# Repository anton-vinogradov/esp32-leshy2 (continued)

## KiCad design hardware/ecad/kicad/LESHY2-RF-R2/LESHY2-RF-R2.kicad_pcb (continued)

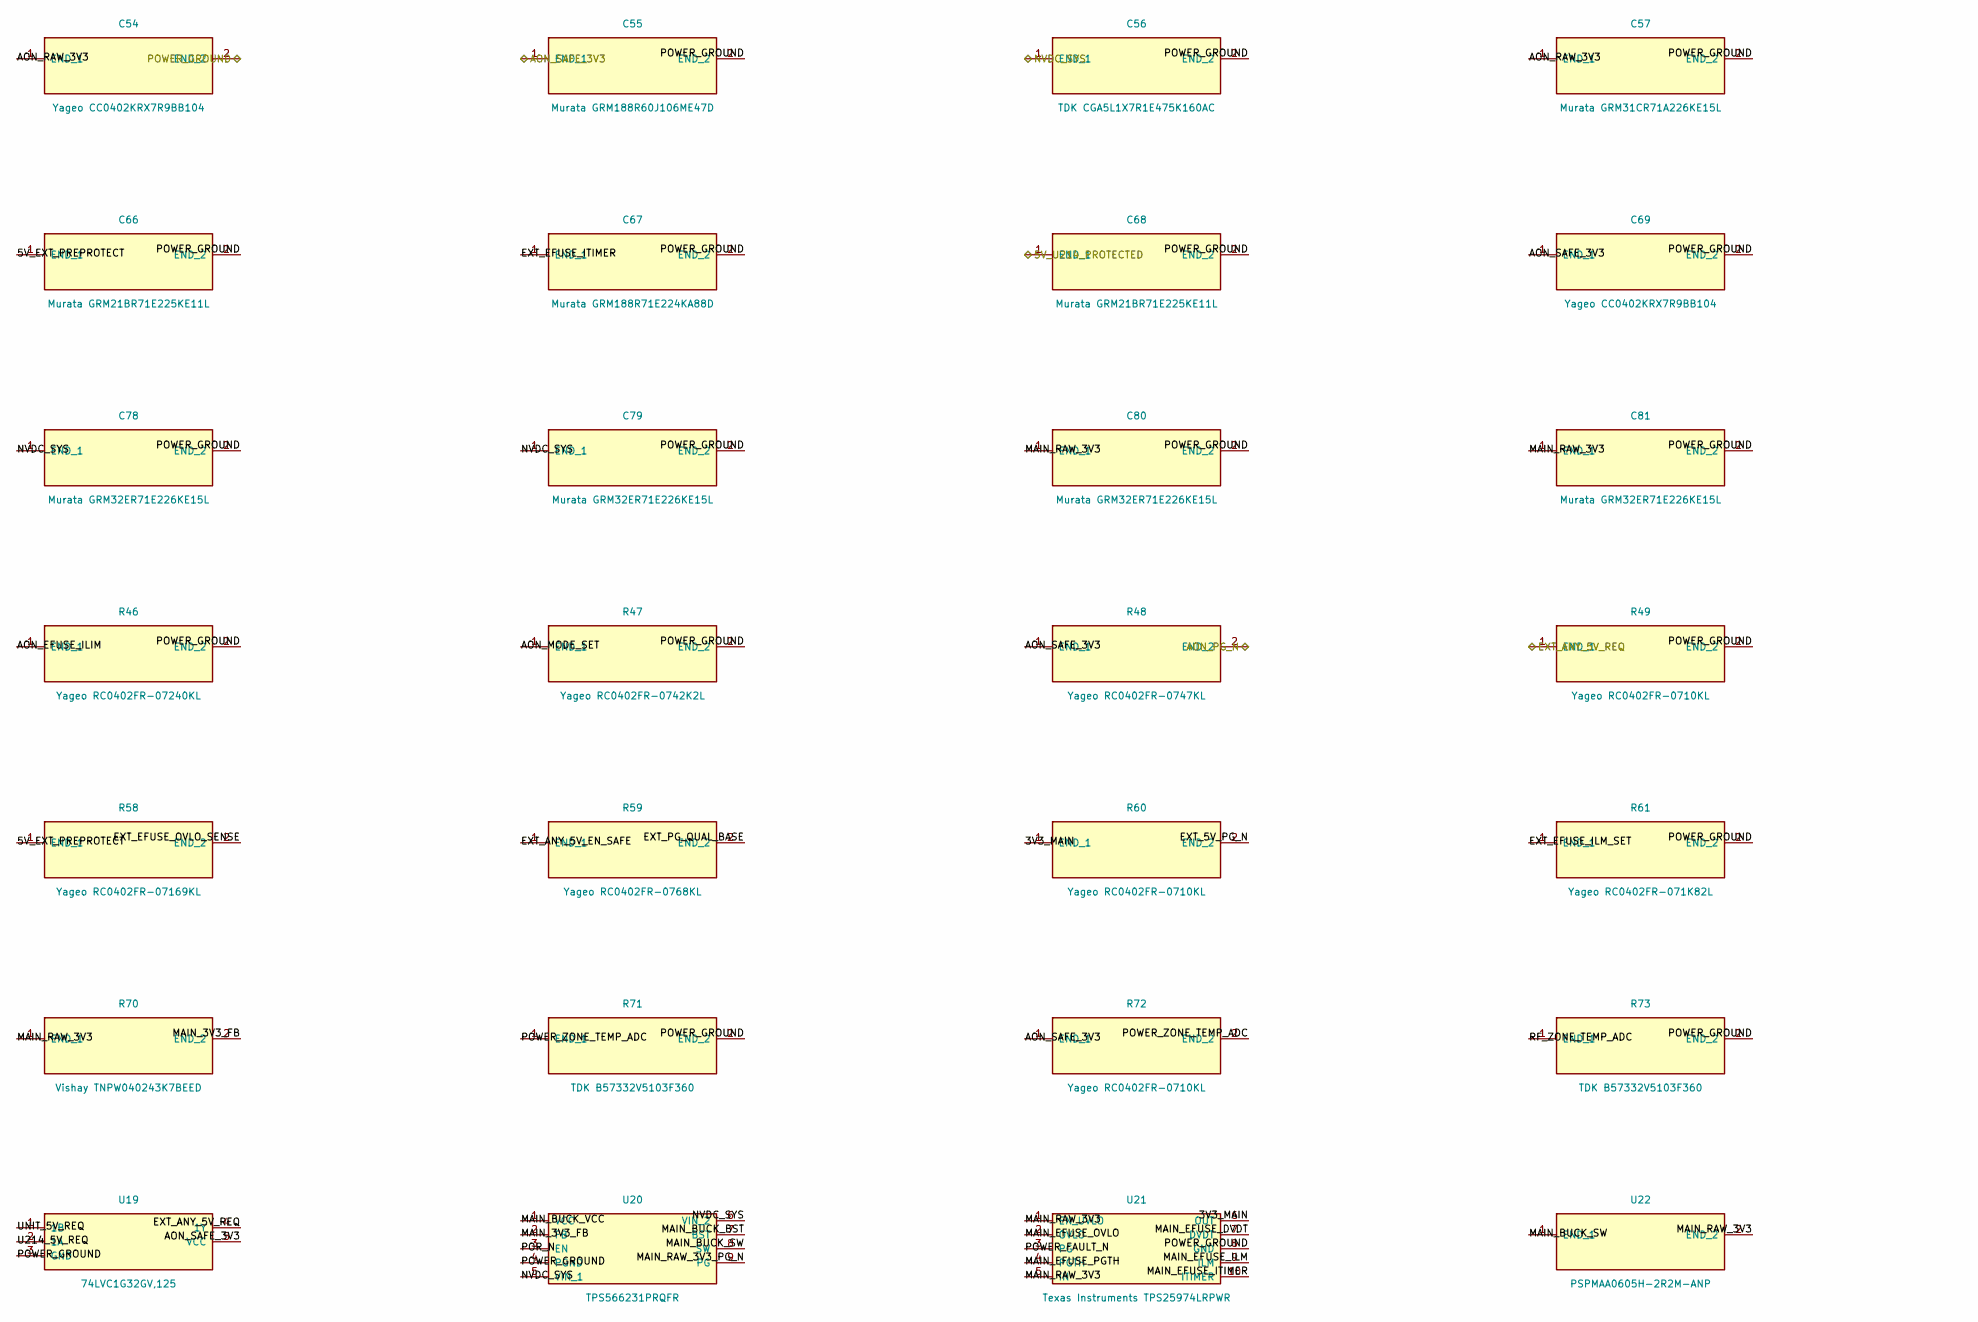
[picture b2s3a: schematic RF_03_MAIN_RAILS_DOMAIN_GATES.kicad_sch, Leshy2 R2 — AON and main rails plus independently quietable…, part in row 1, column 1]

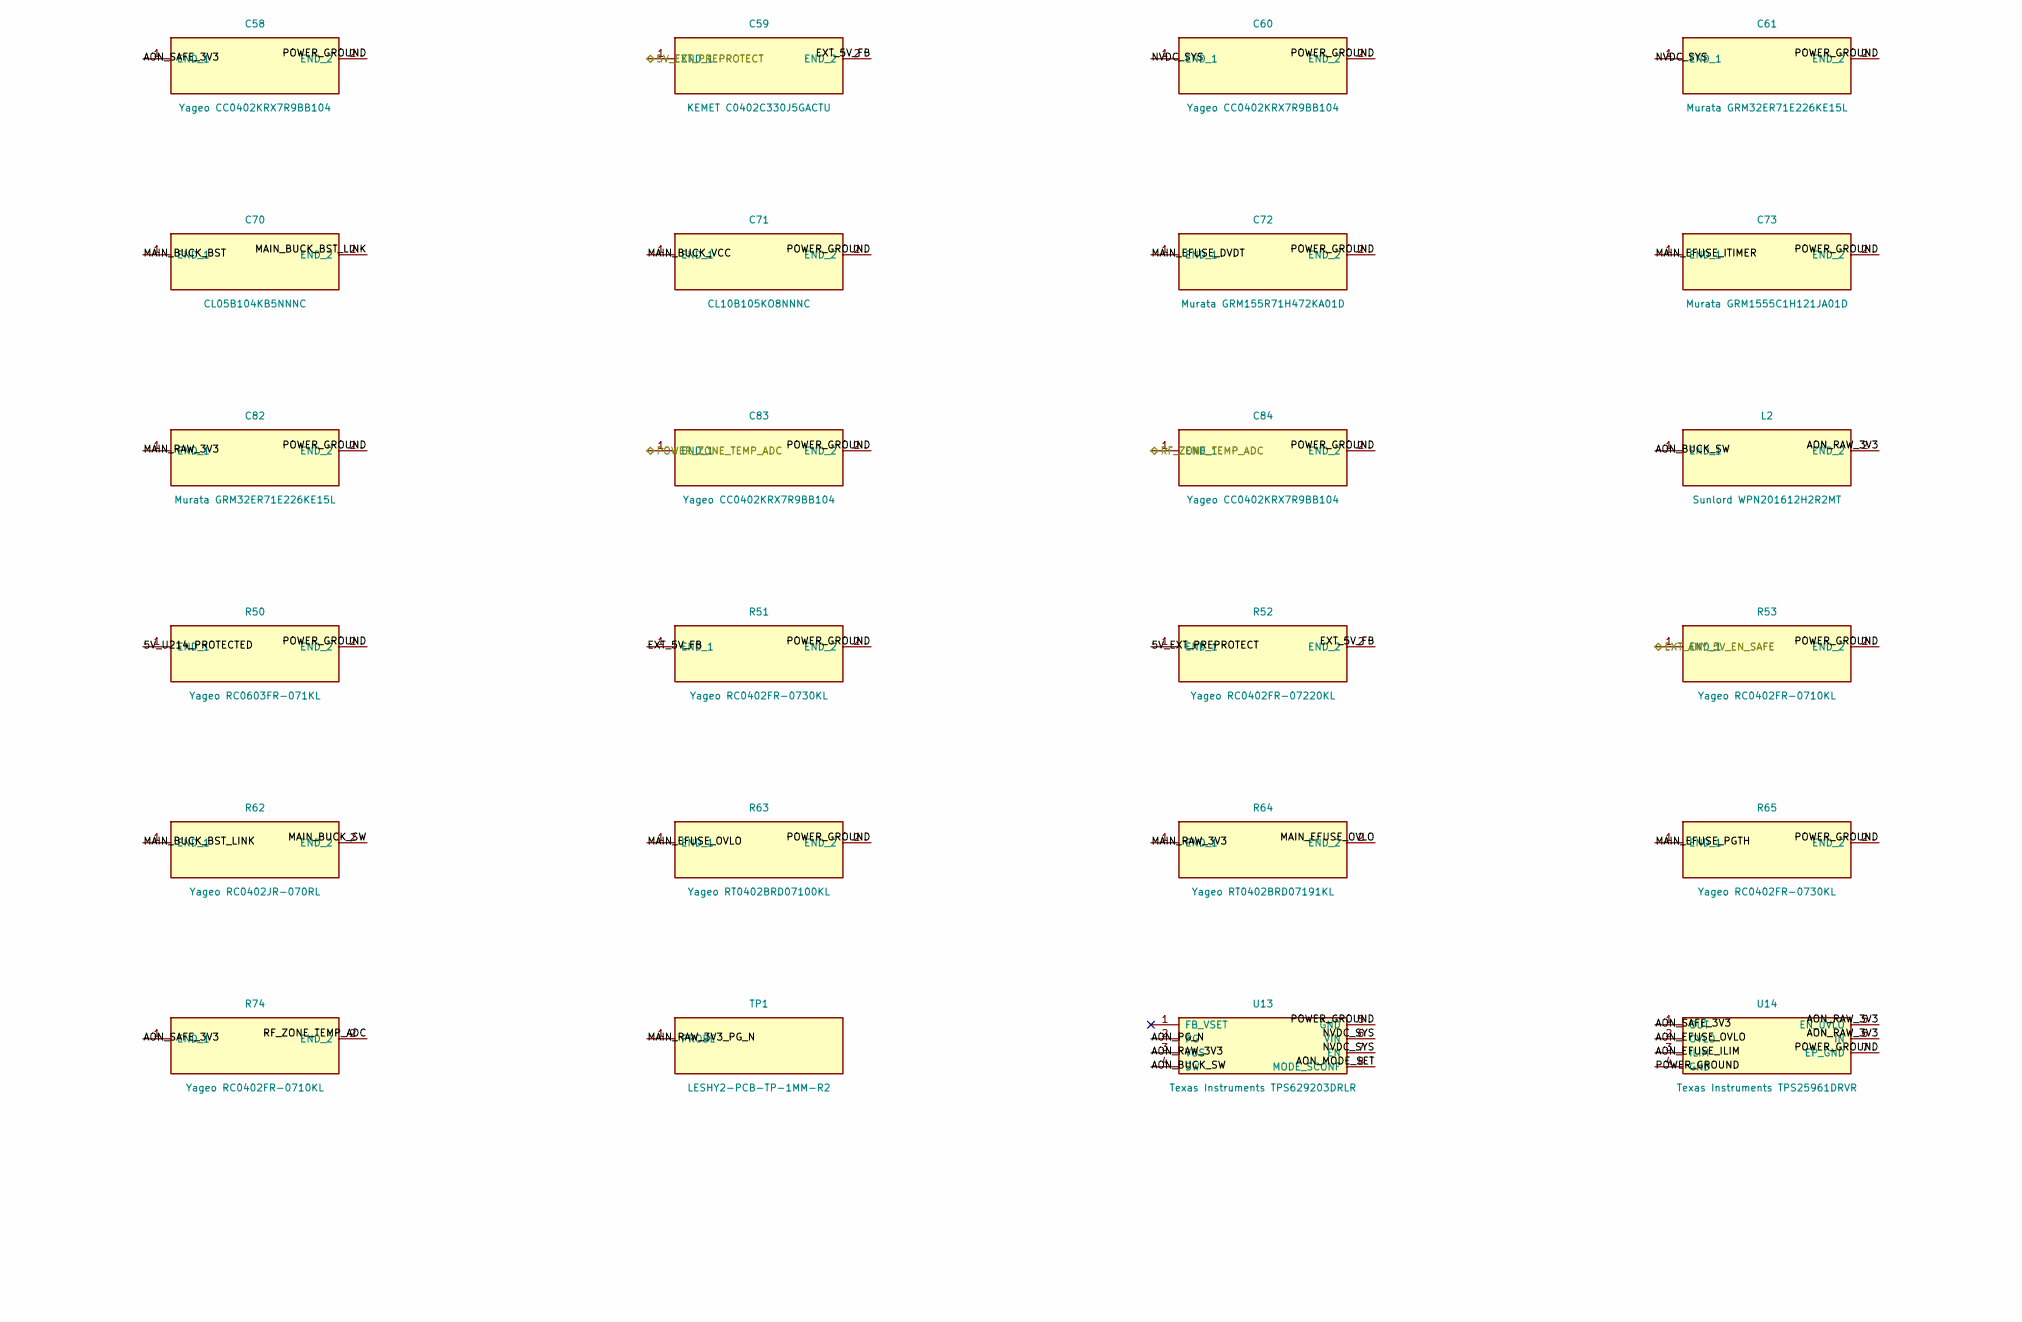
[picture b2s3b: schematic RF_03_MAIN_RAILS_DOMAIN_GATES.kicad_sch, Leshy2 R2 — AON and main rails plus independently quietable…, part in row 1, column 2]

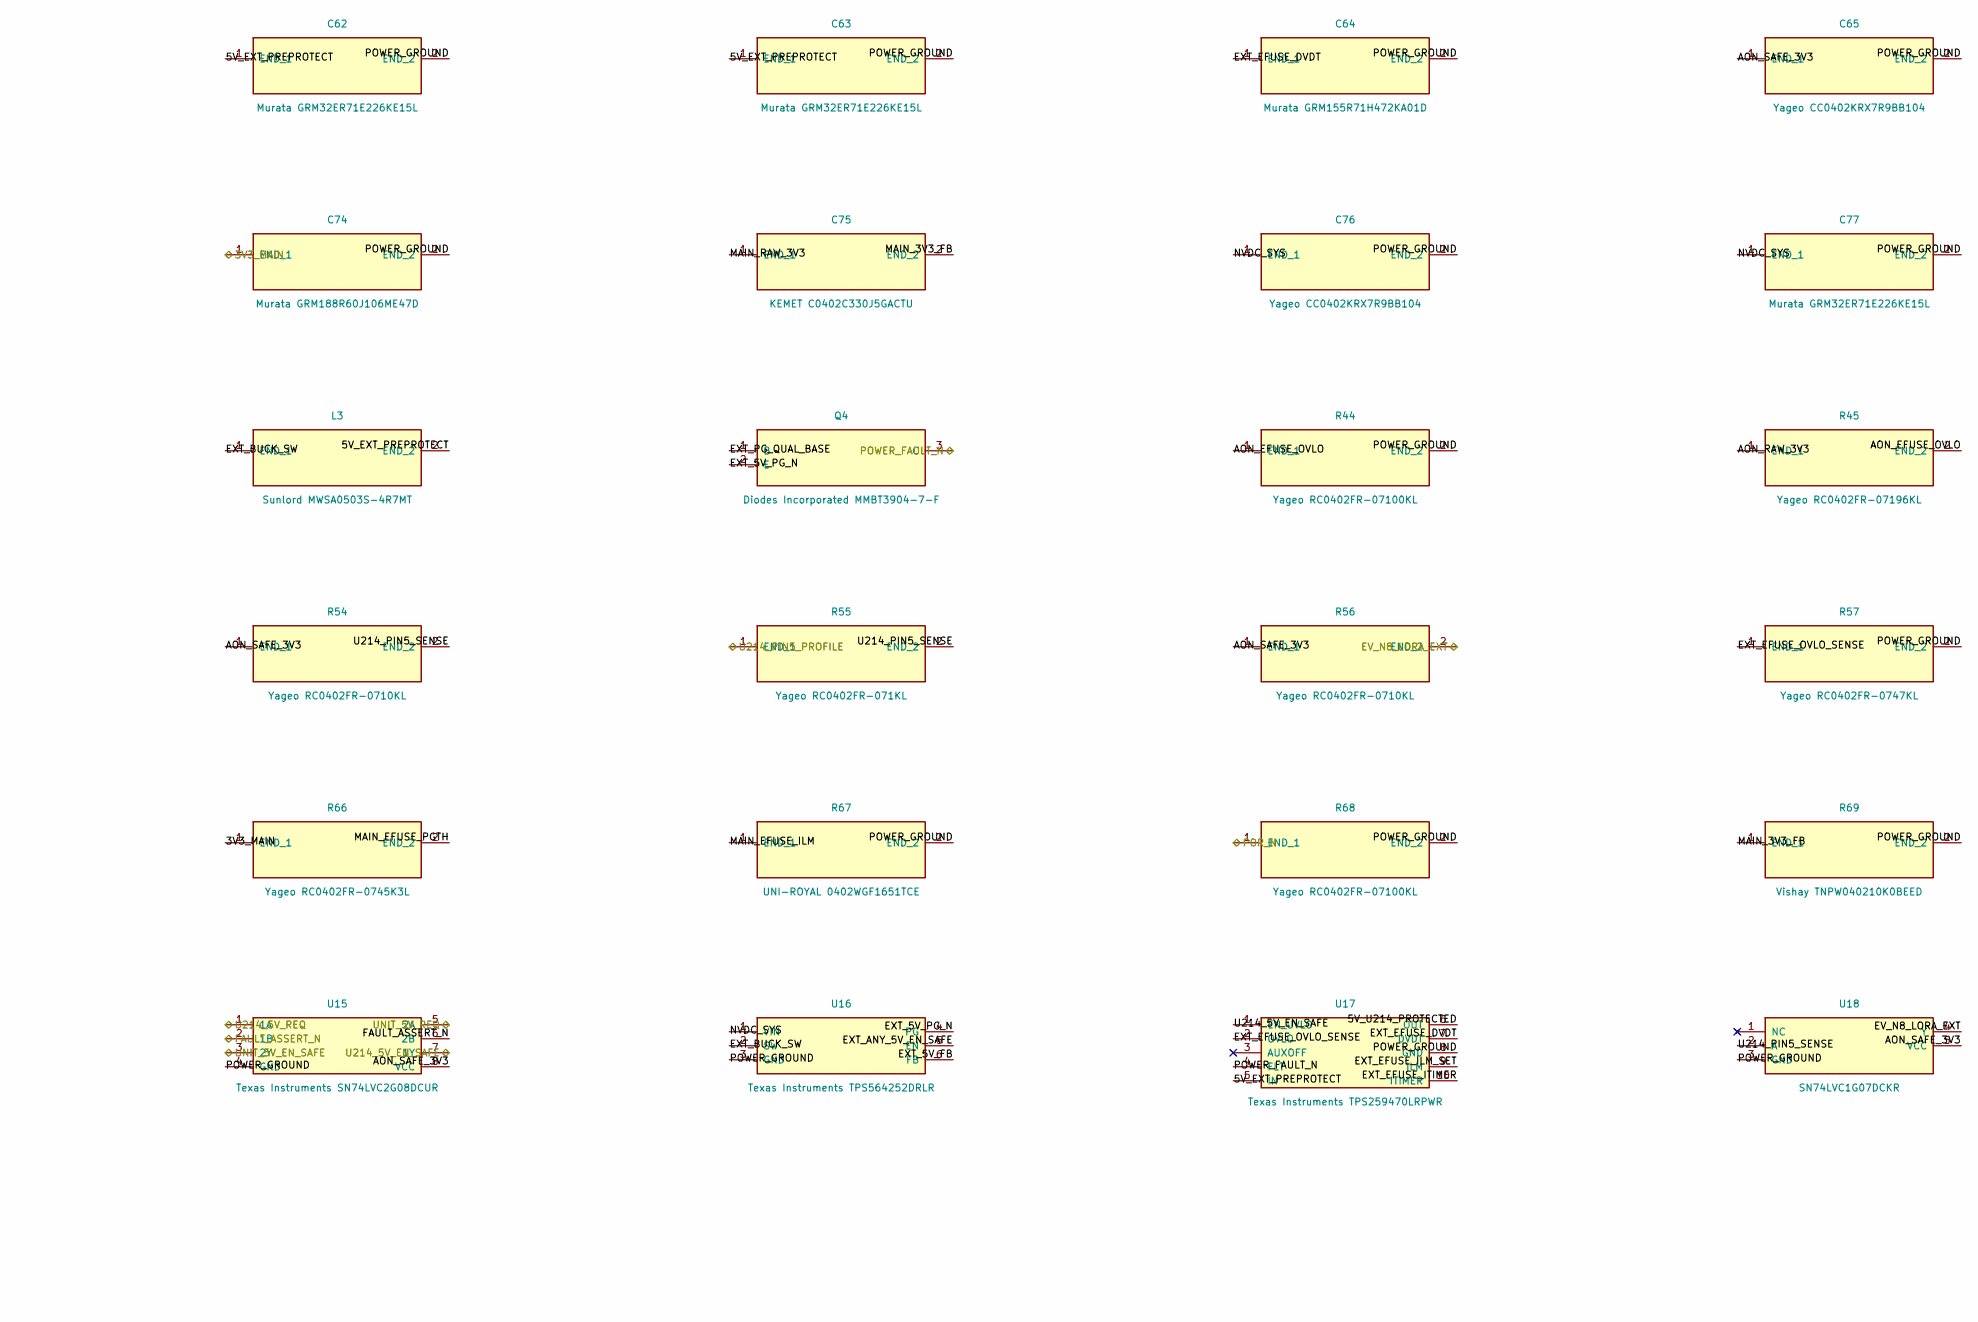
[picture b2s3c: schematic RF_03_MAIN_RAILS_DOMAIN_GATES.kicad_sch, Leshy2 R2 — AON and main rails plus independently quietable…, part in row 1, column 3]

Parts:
C54, C58, C60, C65, C69, C76, C83, C84: Yageo CC0402KRX7R9BB104; C_0402_1005Metric
C55, C74: Murata GRM188R60J106ME47D; C_0603_1608Metric
C56: TDK CGA5L1X7R1E475K160AC; C_1206_3216Metric
C57: Murata GRM31CR71A226KE15L; C_1206_3216Metric
C59, C75: KEMET C0402C330J5GACTU; C_0402_1005Metric
C61, C62, C63, C77, C78, C79, C80, C81, C82: Murata GRM32ER71E226KE15L; C_1210_3225Metric
C64, C72: Murata GRM155R71H472KA01D; C_0402_1005Metric
C66, C68: Murata GRM21BR71E225KE11L; C_0805_2012Metric
C67: Murata GRM188R71E224KA88D; C_0603_1608Metric
C70: CL05B104KB5NNNC; C_0402_1005Metric
C71: CL10B105KO8NNNC; C_0603_1608Metric
C73: Murata GRM1555C1H121JA01D; C_0402_1005Metric
L2: Sunlord WPN201612H2R2MT; L_Murata_LQH2MCNxxxx02_2.0x1.6mm
L3: Sunlord MWSA0503S-4R7MT; L_Sunlord_MWSA0503S
Q4: Diodes Incorporated MMBT3904-7-F; SOT-23
R44, R68: Yageo RC0402FR-07100KL; R_0402_1005Metric
R45: Yageo RC0402FR-07196KL; R_0402_1005Metric
R46: Yageo RC0402FR-07240KL; R_0402_1005Metric
R47: Yageo RC0402FR-0742K2L; R_0402_1005Metric
R48, R57: Yageo RC0402FR-0747KL; R_0402_1005Metric
R49, R53, R54, R56, R60, R72, R74: Yageo RC0402FR-0710KL; R_0402_1005Metric
R50: Yageo RC0603FR-071KL; R_0603_1608Metric
R51, R65: Yageo RC0402FR-0730KL; R_0402_1005Metric
R52: Yageo RC0402FR-07220KL; R_0402_1005Metric
R55: Yageo RC0402FR-071KL; R_0402_1005Metric
R58: Yageo RC0402FR-07169KL; R_0402_1005Metric
R59: Yageo RC0402FR-0768KL; R_0402_1005Metric
R61: Yageo RC0402FR-071K82L; R_0402_1005Metric
R62: Yageo RC0402JR-070RL; R_0402_1005Metric
R63: Yageo RT0402BRD07100KL; R_0402_1005Metric
R64: Yageo RT0402BRD07191KL; R_0402_1005Metric
R66: Yageo RC0402FR-0745K3L; R_0402_1005Metric
R67: UNI-ROYAL 0402WGF1651TCE; R_0402_1005Metric
R69: Vishay TNPW040210K0BEED; R_0402_1005Metric
R70: Vishay TNPW040243K7BEED; R_0402_1005Metric
R71, R73: TDK B57332V5103F360; R_0603_1608Metric
TP1: LESHY2-PCB-TP-1MM-R2; PCB_TestPoint_Pad_D1.0mm
U13: Texas Instruments TPS629203DRLR; TI-DRL0008A-SOT-5X3-8
U14: Texas Instruments TPS25961DRVR; WSON-6-1EP_2x2mm_P0.65mm_EP1x1.6mm
U15: Texas Instruments SN74LVC2G08DCUR; VSSOP-8_2.3x2mm_P0.5mm
U16: Texas Instruments TPS564252DRLR; Texas_R-PDSO-N6_DRL-6
U17: Texas Instruments TPS259470LRPWR; TI-RPW0010A-VQFN-HR-10
U18: SN74LVC1G07DCKR; Texas_R-PDSO-G5_DCK-5
U19: 74LVC1G32GV,125; SC-74A-5_1.55x2.9mm_P0.95mm
U20: TPS566231PRQFR; Texas_RQF0009A_1.5x2.0mm
U21: Texas Instruments TPS25974LRPWR; TI-RPW0010A-VQFN-HR-10
U22: PSPMAA0605H-2R2M-ANP; PRODTech_PSPMAA0605H_7.1x6.6mm

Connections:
/RF_01_USB_PD_CHARGE/AON_SAFE_3V3: C55.1 (END_1), C58.1 (END_1), C65.1 (END_1), C69.1 (END_1), R48.1 (END_1), R54.1 (END_1), R56.1 (END_1), R72.1 (END_1), R74.1 (END_1), U14.1 (OUT), U15.8 (VCC), U18.5 (VCC), U19.5 (VCC); also elsewhere on the board
/RF_01_USB_PD_CHARGE/NVDC_SYS: C56.1 (END_1), C60.1 (END_1), C61.1 (END_1), C76.1 (END_1), C77.1 (END_1), C78.1 (END_1), C79.1 (END_1), U13.6 (VIN), U13.7 (EN), U16.1 (VIN), U20.5 (VIN_1), U20.6 (VIN_2); also elsewhere on the board
/RF_01_USB_PD_CHARGE/POWER_GROUND: C54.2 (END_2), C55.2 (END_2), C56.2 (END_2), C57.2 (END_2), C58.2 (END_2), C60.2 (END_2), C61.2 (END_2), C62.2 (END_2), C63.2 (END_2), C64.2 (END_2), C65.2 (END_2), C66.2 (END_2), C67.2 (END_2), C68.2 (END_2), C69.2 (END_2), C71.2 (END_2), C72.2 (END_2), C73.2 (END_2), C74.2 (END_2), C76.2 (END_2), C77.2 (END_2), C78.2 (END_2), C79.2 (END_2), C80.2 (END_2), C81.2 (END_2), C82.2 (END_2), C83.2 (END_2), C84.2 (END_2), R44.2 (END_2), R46.2 (END_2), R47.2 (END_2), R49.2 (END_2), R50.2 (END_2), R51.2 (END_2), R53.2 (END_2), R57.2 (END_2), R61.2 (END_2), R63.2 (END_2), R65.2 (END_2), R67.2 (END_2), R68.2 (END_2), R69.2 (END_2), R71.2 (END_2), R73.2 (END_2), U13.5 (GND), U14.4 (GND), U14.7 (EP_GND), U15.4 (GND), U16.3 (GND), U17.8 (GND), U18.3 (GND), U19.3 (GND), U20.4 (PGND), U21.8 (GND); also elsewhere on the board
/RF_02_PACK_SAFETY_AON/3V3_MAIN: C74.1 (END_1), R60.1 (END_1), R66.1 (END_1), U21.6 (OUT); also elsewhere on the board
/RF_03_MAIN_RAILS_DOMAIN_GATES/5V_EXT_PREPROTECT: C59.1 (END_1), C62.1 (END_1), C63.1 (END_1), C66.1 (END_1), L3.2 (END_2), R52.1 (END_1), R58.1 (END_1), U17.5 (IN); also elsewhere on the board
/RF_03_MAIN_RAILS_DOMAIN_GATES/5V_U214_PROTECTED: C68.1 (END_1), R50.1 (END_1), U17.6 (OUT); also elsewhere on the board
/RF_03_MAIN_RAILS_DOMAIN_GATES/AON_BUCK_SW: L2.1 (END_1), U13.4 (SW)
/RF_03_MAIN_RAILS_DOMAIN_GATES/AON_EFUSE_ILIM: R46.1 (END_1), U14.3 (ILIM)
/RF_03_MAIN_RAILS_DOMAIN_GATES/AON_EFUSE_OVLO: R44.1 (END_1), R45.2 (END_2), U14.2 (OVLO)
/RF_03_MAIN_RAILS_DOMAIN_GATES/AON_MODE_SET: R47.1 (END_1), U13.8 (MODE_SCONF)
/RF_03_MAIN_RAILS_DOMAIN_GATES/AON_PG_N: R48.2 (END_2), U13.2 (PG); also elsewhere on the board
/RF_03_MAIN_RAILS_DOMAIN_GATES/AON_RAW_3V3: C54.1 (END_1), C57.1 (END_1), L2.2 (END_2), R45.1 (END_1), U13.3 (VOS), U14.5 (EN_UVLO), U14.6 (IN)
/RF_03_MAIN_RAILS_DOMAIN_GATES/EV_N8_LORA_EXT: R56.2 (END_2), U18.4 (Y); also elsewhere on the board
/RF_03_MAIN_RAILS_DOMAIN_GATES/EXT_5V_FB: C59.2 (END_2), R51.1 (END_1), R52.2 (END_2), U16.6 (FB)
/RF_03_MAIN_RAILS_DOMAIN_GATES/EXT_5V_PG_N: Q4.2 (E), R60.2 (END_2), U16.4 (PG)
/RF_03_MAIN_RAILS_DOMAIN_GATES/EXT_ANY_5V_EN_SAFE: R53.1 (END_1), R59.1 (END_1), U16.5 (EN); also elsewhere on the board
/RF_03_MAIN_RAILS_DOMAIN_GATES/EXT_ANY_5V_REQ: R49.1 (END_1), U19.4 (1Y); also elsewhere on the board
/RF_03_MAIN_RAILS_DOMAIN_GATES/EXT_BUCK_SW: L3.1 (END_1), U16.2 (SW)
/RF_03_MAIN_RAILS_DOMAIN_GATES/EXT_EFUSE_DVDT: C64.1 (END_1), U17.7 (DVDT)
/RF_03_MAIN_RAILS_DOMAIN_GATES/EXT_EFUSE_ILM_SET: R61.1 (END_1), U17.9 (ILM)
/RF_03_MAIN_RAILS_DOMAIN_GATES/EXT_EFUSE_ITIMER: C67.1 (END_1), U17.10 (ITIMER)
/RF_03_MAIN_RAILS_DOMAIN_GATES/EXT_EFUSE_OVLO_SENSE: R57.1 (END_1), R58.2 (END_2), U17.2 (OVLO)
/RF_03_MAIN_RAILS_DOMAIN_GATES/EXT_PG_QUAL_BASE: Q4.1 (B), R59.2 (END_2)
/RF_03_MAIN_RAILS_DOMAIN_GATES/FAULT_ASSERT_N: U15.2 (1B), U15.6 (2B); also elsewhere on the board
/RF_03_MAIN_RAILS_DOMAIN_GATES/MAIN_3V3_FB: C75.2 (END_2), R69.1 (END_1), R70.2 (END_2), U20.2 (FB)
/RF_03_MAIN_RAILS_DOMAIN_GATES/MAIN_BUCK_BST: C70.1 (END_1), U20.7 (BST)
/RF_03_MAIN_RAILS_DOMAIN_GATES/MAIN_BUCK_BST_LINK: C70.2 (END_2), R62.1 (END_1)
/RF_03_MAIN_RAILS_DOMAIN_GATES/MAIN_BUCK_SW: R62.2 (END_2), U20.8 (SW), U22.1 (END_1)
/RF_03_MAIN_RAILS_DOMAIN_GATES/MAIN_BUCK_VCC: C71.1 (END_1), U20.1 (VCC)
/RF_03_MAIN_RAILS_DOMAIN_GATES/MAIN_EFUSE_DVDT: C72.1 (END_1), U21.7 (DVDT)
/RF_03_MAIN_RAILS_DOMAIN_GATES/MAIN_EFUSE_ILM: R67.1 (END_1), U21.9 (ILM)
/RF_03_MAIN_RAILS_DOMAIN_GATES/MAIN_EFUSE_ITIMER: C73.1 (END_1), U21.10 (ITIMER)
/RF_03_MAIN_RAILS_DOMAIN_GATES/MAIN_EFUSE_OVLO: R63.1 (END_1), R64.2 (END_2), U21.2 (OVLO)
/RF_03_MAIN_RAILS_DOMAIN_GATES/MAIN_EFUSE_PGTH: R65.1 (END_1), R66.2 (END_2), U21.4 (PGTH)
/RF_03_MAIN_RAILS_DOMAIN_GATES/MAIN_RAW_3V3: C75.1 (END_1), C80.1 (END_1), C81.1 (END_1), C82.1 (END_1), R64.1 (END_1), R70.1 (END_1), U21.1 (EN_UVLO), U21.5 (IN), U22.2 (END_2)
/RF_03_MAIN_RAILS_DOMAIN_GATES/MAIN_RAW_3V3_PG_N: TP1.1, U20.9 (PG)
/RF_03_MAIN_RAILS_DOMAIN_GATES/POR_N: R68.1 (END_1), U20.3 (EN); also elsewhere on the board
/RF_03_MAIN_RAILS_DOMAIN_GATES/POWER_FAULT_N: Q4.3 (C), U17.4 (FLT), U21.3 (PG); also elsewhere on the board
/RF_03_MAIN_RAILS_DOMAIN_GATES/POWER_ZONE_TEMP_ADC: C83.1 (END_1), R71.1 (END_1), R72.2 (END_2); also elsewhere on the board
/RF_03_MAIN_RAILS_DOMAIN_GATES/RF_ZONE_TEMP_ADC: C84.1 (END_1), R73.1 (END_1), R74.2 (END_2); also elsewhere on the board
/RF_03_MAIN_RAILS_DOMAIN_GATES/U214_5V_EN_SAFE: U15.7 (1Y), U17.1 (EN_UVLO); also elsewhere on the board
/RF_03_MAIN_RAILS_DOMAIN_GATES/U214_5V_REQ: U15.1 (1A), U19.2 (1A); also elsewhere on the board
/RF_03_MAIN_RAILS_DOMAIN_GATES/U214_PIN5_SENSE: R54.2 (END_2), R55.2 (END_2), U18.2 (A)
/RF_03_MAIN_RAILS_DOMAIN_GATES/UNIT_5V_REQ: U15.5 (2A), U19.1 (1B); also elsewhere on the board
/RF_30_U214_U219_M5_EXT/U214_PIN5_PROFILE: R55.1 (END_1); also elsewhere on the board
/RF_30_U214_U219_M5_EXT/UNIT_5V_EN_SAFE: U15.3 (2Y); also elsewhere on the board
